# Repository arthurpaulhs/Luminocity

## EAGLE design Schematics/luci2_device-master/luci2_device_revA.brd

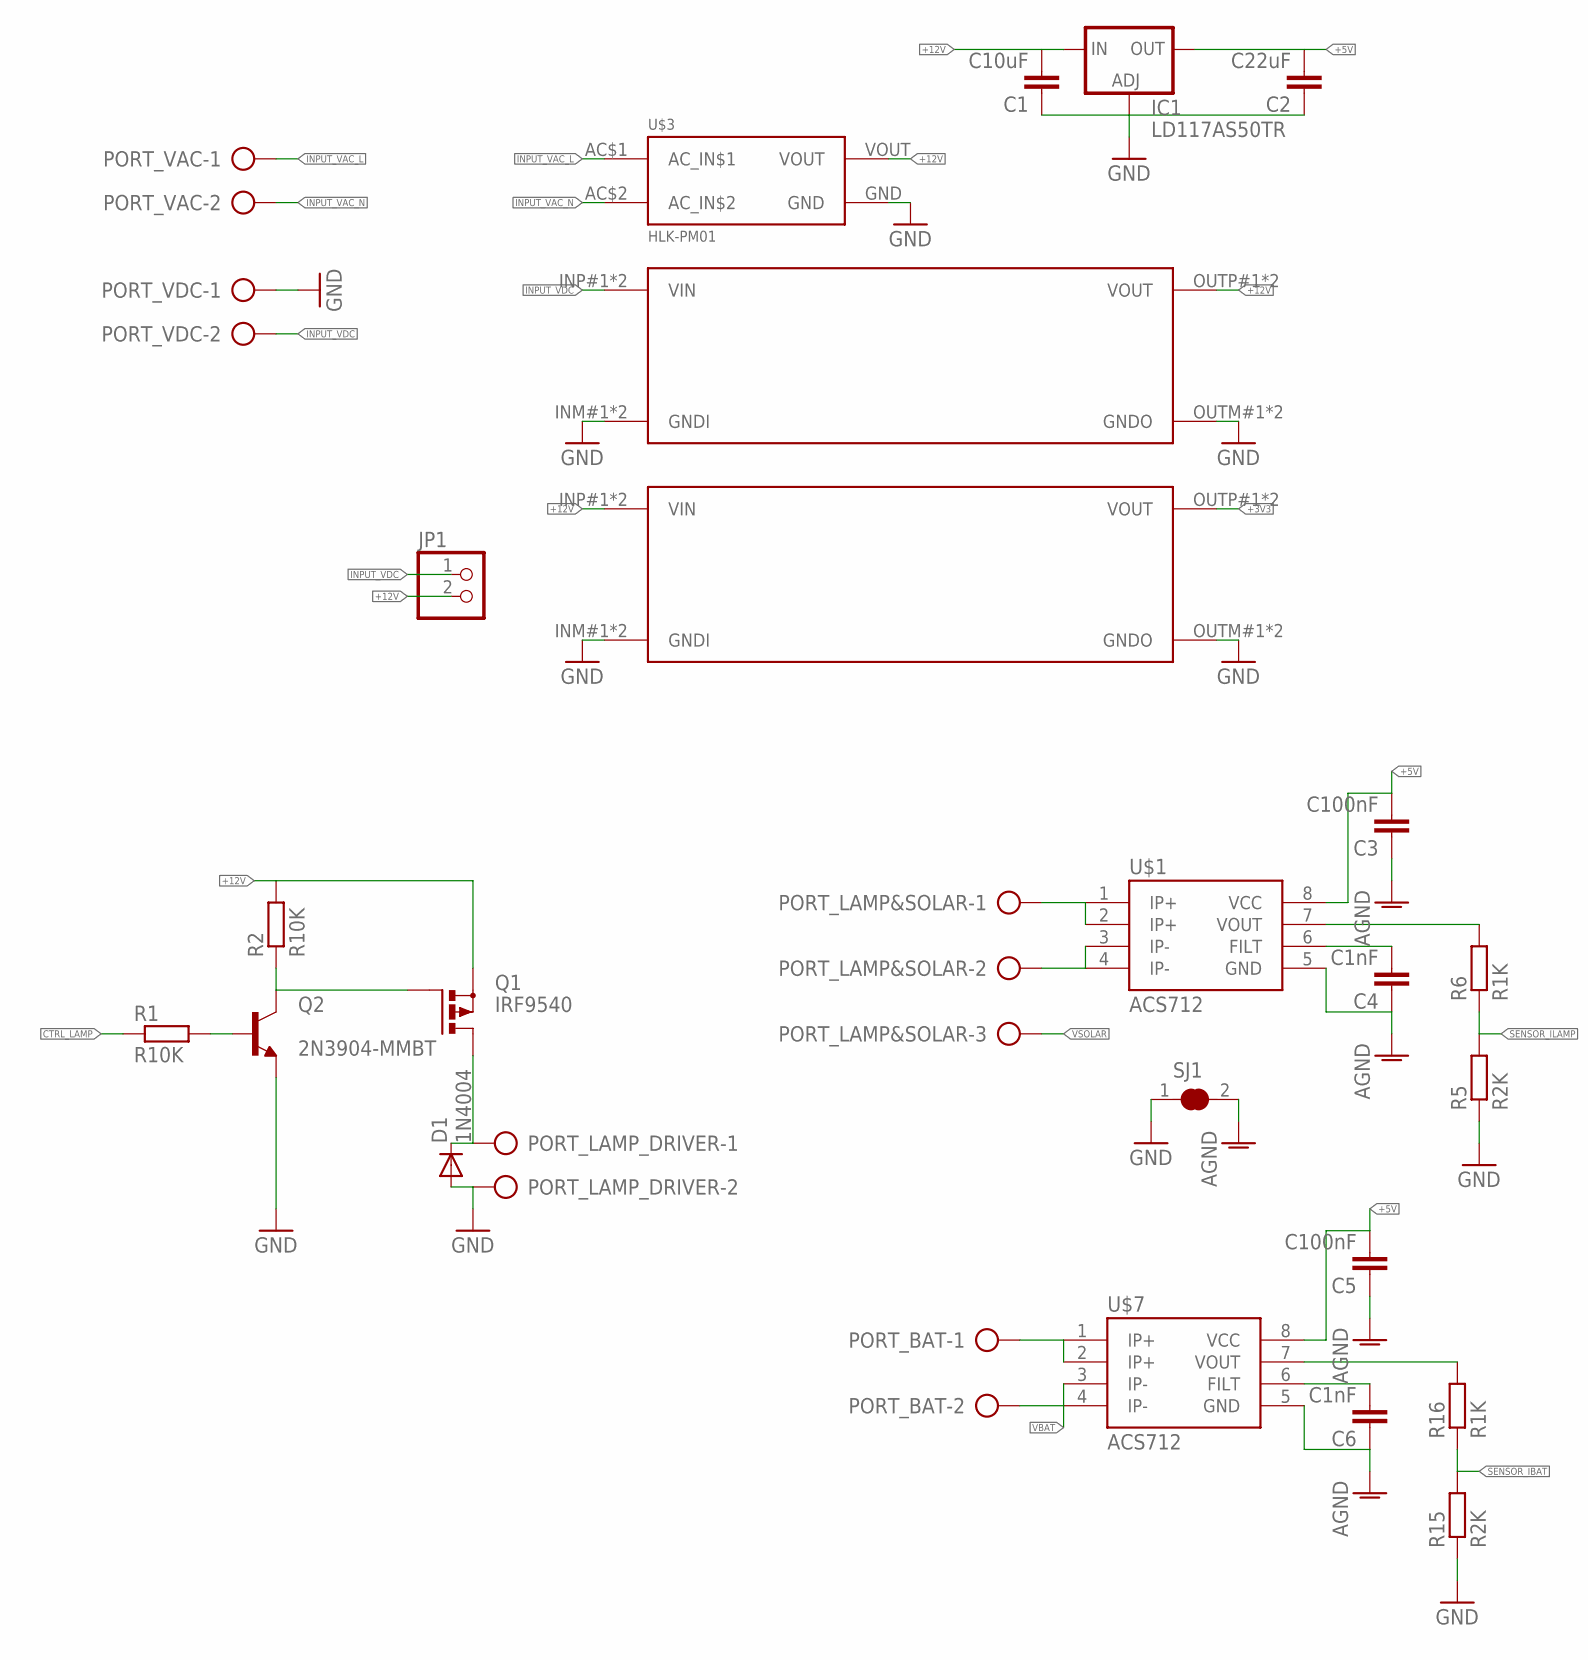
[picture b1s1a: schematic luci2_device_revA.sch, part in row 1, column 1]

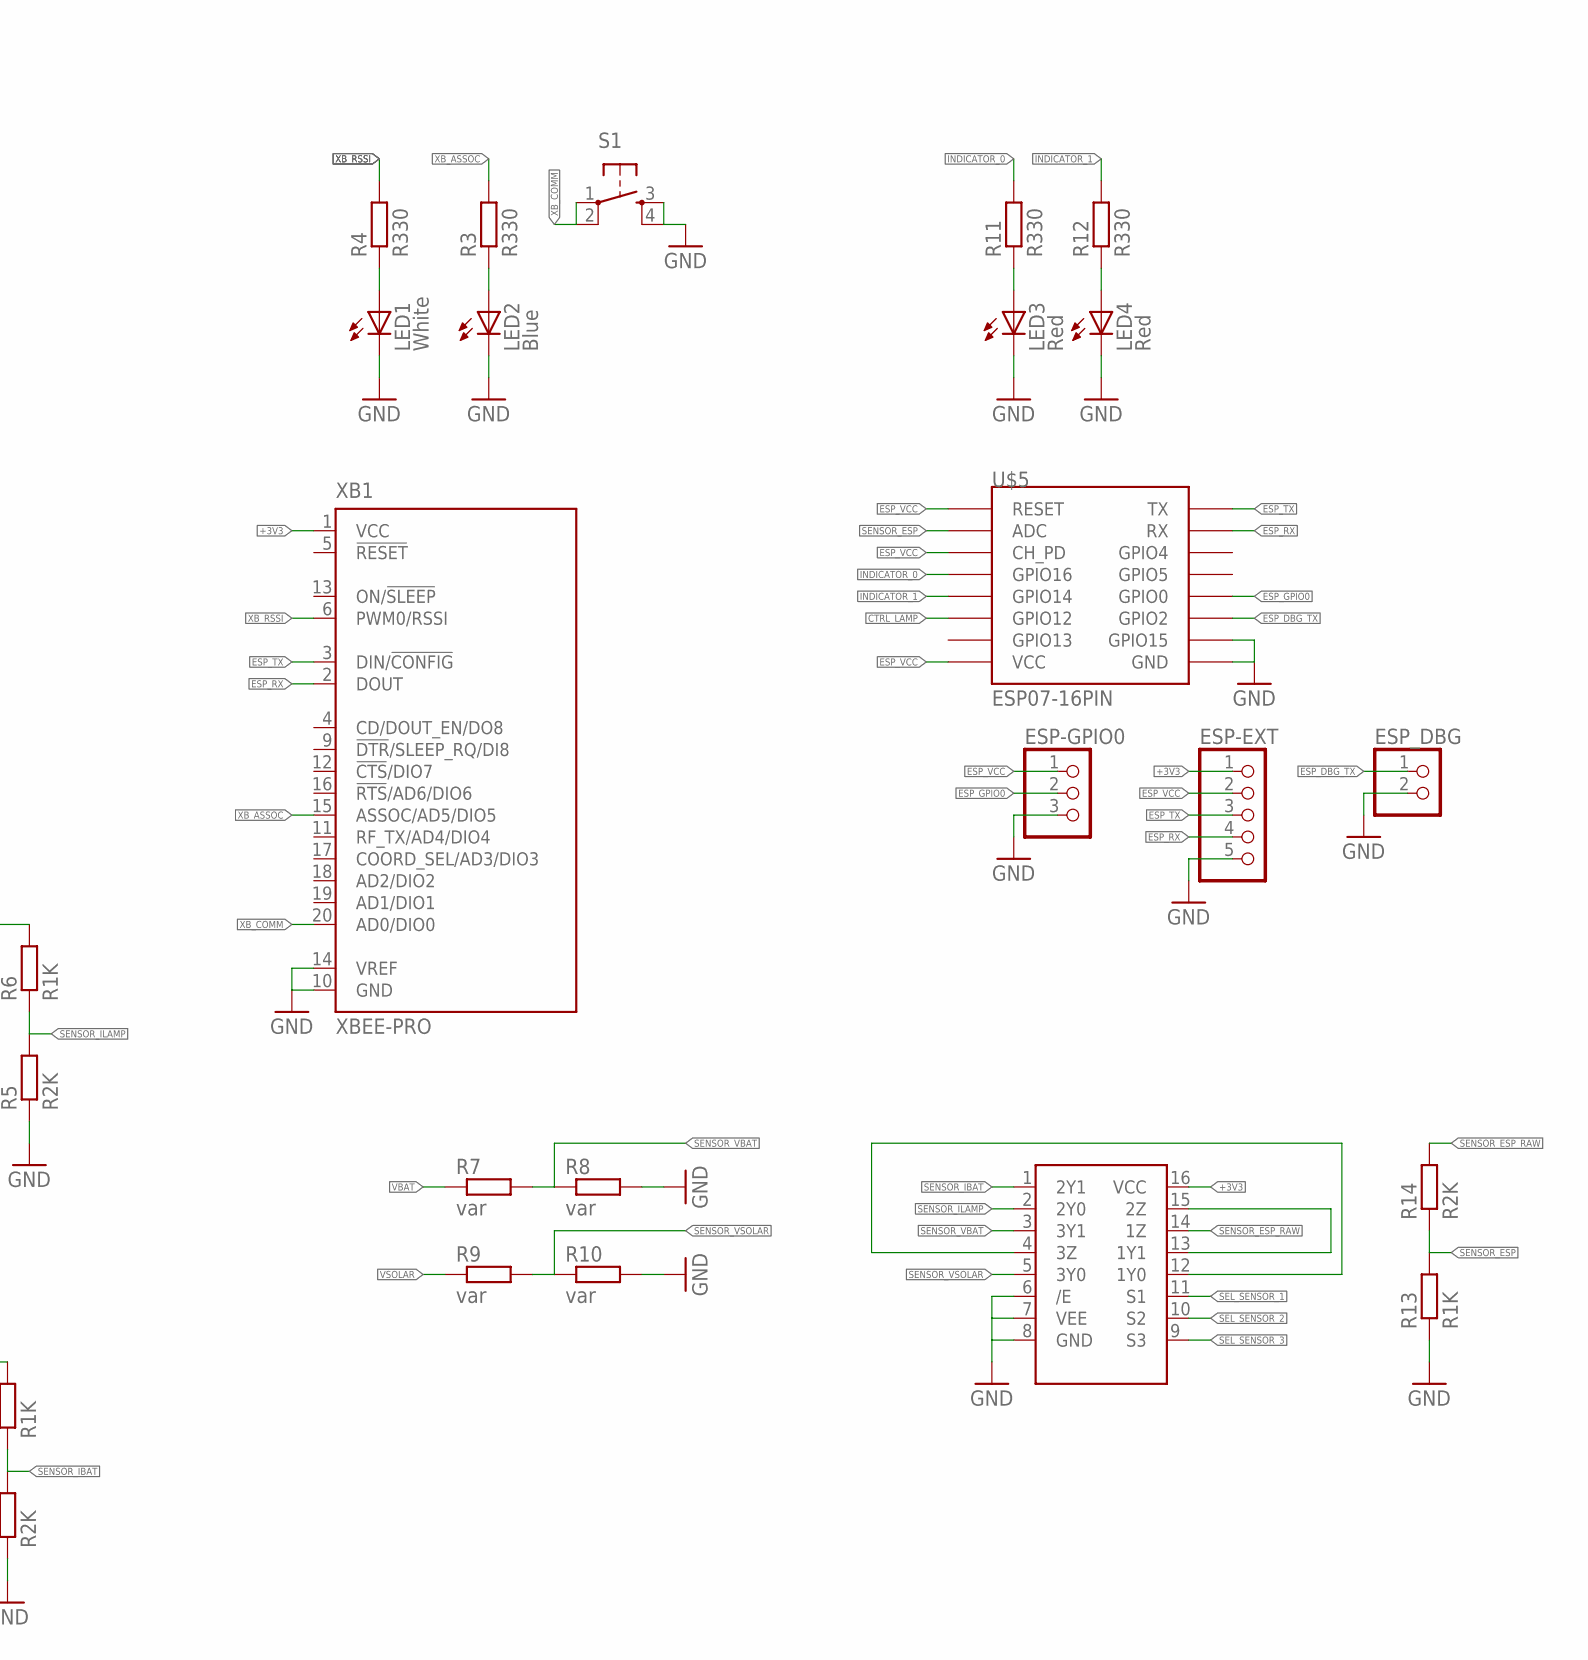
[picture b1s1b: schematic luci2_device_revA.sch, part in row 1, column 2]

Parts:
C1: C10uF; C0805
C2: C22uF; C0805
C3, C5: C100nF; C0805
C4, C6: C1nF; C0805
D1: 1N4004; DO41-10
ESP-EXT: HEADER-1X5ROUND; 1X05_ROUND
ESP-GPIO0: HEADER-1X3ROUND; 1X03_ROUND
ESP_DBG: HEADER-1X2ROUND; 1X02_ROUND
IC1: LD117AS50TR; SOT223
JP1: HEADER-1X2ROUND; 1X02_ROUND
LED1: White; CHIPLED_0805
LED2: Blue; CHIPLED_0805
LED3, LED4: Red; CHIPLED_0805
PORT_BAT: AK300/2
PORT_LAMP&SOLAR: AK300/3
PORT_LAMP_DRIVER: AK300/2
PORT_VAC: AK300/2
PORT_VDC: AK300/2
Q1: IRF9540; TO220BV
Q2: 2N3904-MMBT; SOT23
R1, R2: R10K; M0805
R3, R4, R11, R12: R330; M0805
R5, R14, R15: R2K; M0805
R6, R13, R16: R1K; M0805
R7, R8, R9, R10: var; M0805
S1: TAC_SWITCHPTH; TACTILE-PTH
SJ1: SOLDERJUMPER_CLOSED; SOLDERJUMPER_CLOSEDWIRE
U$1, U$7: ACS712; SO08
U$2, U$4: DCDCMODULE_SMALL; DCDCMODULE-SMALL
U$3: HLK-PM01
U$5: ESP07-16PIN
U$6: 74HC4053D; SO16
XB1: XBEE-PRO

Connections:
+3V3: ESP-EXT.1, U$2.OUTP#1 (VOUT), U$2.OUTP#2 (VOUT), U$6.16 (VCC), XB1.1 (VCC)
+5V: C2.2, C3.2, C5.2, IC1.4 (OUT), U$1.8 (VCC), U$7.8 (VCC)
+12V: C1.2, IC1.3 (IN), JP1.2, Q1.S, R2.2, U$2.INP#1 (VIN), U$2.INP#2 (VIN), U$3.VOUT, U$4.OUTP#1 (VOUT), U$4.OUTP#2 (VOUT)
AGND: C3.1, C4.1, C5.1, C6.1, SJ1.2, U$1.5 (GND), U$7.5 (GND)
CTRL_LAMP: R1.1, U$5.GPIO12
ESP_DBG_TX: ESP_DBG.1, U$5.GPIO2
ESP_GPIO0: ESP-GPIO0.2, U$5.GPIO0
ESP_RX: ESP-EXT.4, U$5.RX, XB1.2 (DOUT)
ESP_TX: ESP-EXT.3, U$5.TX, XB1.3 (DIN/!CONFIG)
ESP_VCC: ESP-EXT.2, ESP-GPIO0.1, U$5.CH_PD, U$5.REST (RESET), U$5.VCC
GND: C1.1, C2.1, D1.A, ESP-EXT.5, ESP-GPIO0.3, ESP_DBG.2, IC1.1 (ADJ), LED1.C, LED2.C, LED3.C, LED4.C, PORT_LAMP_DRIVER.2, PORT_VDC.1, Q2.2 (E), R5.1, R8.2, R10.2, R13.1, R15.1, S1.3, S1.4, SJ1.1, U$2.INM#1 (GNDI), U$2.INM#2 (GNDI), U$2.OUTM#1 (GNDO), U$2.OUTM#2 (GNDO), U$3.GND, U$4.INM#1 (GNDI), U$4.INM#2 (GNDI), U$4.OUTM#1 (GNDO), U$4.OUTM#2 (GNDO), U$5.GND, U$5.GPIO15, U$6.6 (/E), U$6.7 (VEE), U$6.8 (GND), XB1.10 (GND), XB1.14 (VREF)
INDICATOR_0: R11.2, U$5.GPIO16
INDICATOR_1: R12.2, U$5.GPIO14
INPUT_VAC_L: PORT_VAC.1, U$3.AC$1 (AC_IN$1)
INPUT_VAC_N: PORT_VAC.2, U$3.AC$2 (AC_IN$2)
INPUT_VDC: JP1.1, PORT_VDC.2, U$4.INP#1 (VIN), U$4.INP#2 (VIN)
unnamed: D1.C, PORT_LAMP_DRIVER.1, Q1.D
unnamed: Q1.G, Q2.3 (C), R2.1
unnamed: LED1.A, R4.1
unnamed: Q2.1 (B), R1.2
unnamed: LED2.A, R3.1
unnamed: U$6.13 (1Y1), U$6.15 (2Z)
unnamed: R6.2, U$1.7 (VOUT)
unnamed: PORT_LAMP&SOLAR.1, U$1.1 (IP+), U$1.2 (IP+)
unnamed: U$6.4 (3Z), U$6.12 (1Y0)
unnamed: PORT_LAMP&SOLAR.2, U$1.3 (IP-), U$1.4 (IP-)
unnamed: C4.2, U$1.6 (FILT)
unnamed: PORT_BAT.1, U$7.1 (IP+), U$7.2 (IP+)
unnamed: C6.2, U$7.6 (FILT)
unnamed: R16.2, U$7.7 (VOUT)
unnamed: LED3.A, R11.1
unnamed: LED4.A, R12.1
SEL_SENSOR_1: U$6.11 (S1)
SEL_SENSOR_2: U$6.10 (S2)
SEL_SENSOR_3: U$6.9 (S3)
SENSOR_ESP: R13.2, R14.1, U$5.ADC
SENSOR_ESP_RAW: R14.2, U$6.14 (1Z)
SENSOR_IBAT: R15.2, R16.1, U$6.1 (2Y1)
SENSOR_ILAMP: R5.2, R6.1, U$6.2 (2Y0)
SENSOR_VBAT: R7.2, R8.1, U$6.3 (3Y1)
SENSOR_VSOLAR: R9.2, R10.1, U$6.5 (3Y0)
VBAT: PORT_BAT.2, R7.1, U$7.3 (IP-), U$7.4 (IP-)
VSOLAR: PORT_LAMP&SOLAR.3, R9.1
XB_ASSOC: R3.2, XB1.15 (ASSOC/AD5/DIO5)
XB_COMM: S1.1, S1.2, XB1.20 (AD0/DIO0)
XB_RSSI: R4.2, XB1.6 (PWM0/RSSI)

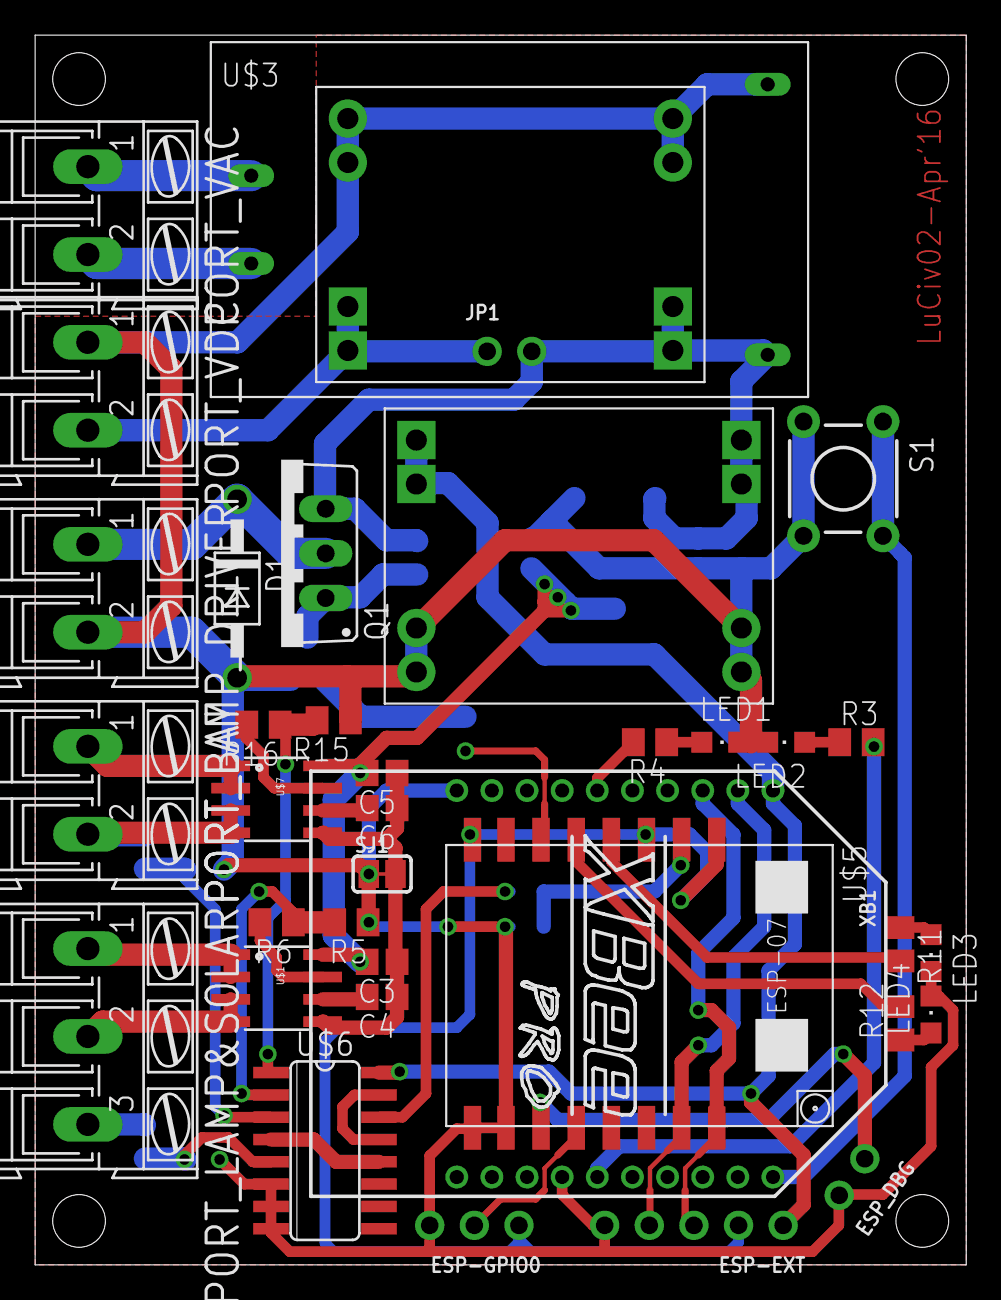
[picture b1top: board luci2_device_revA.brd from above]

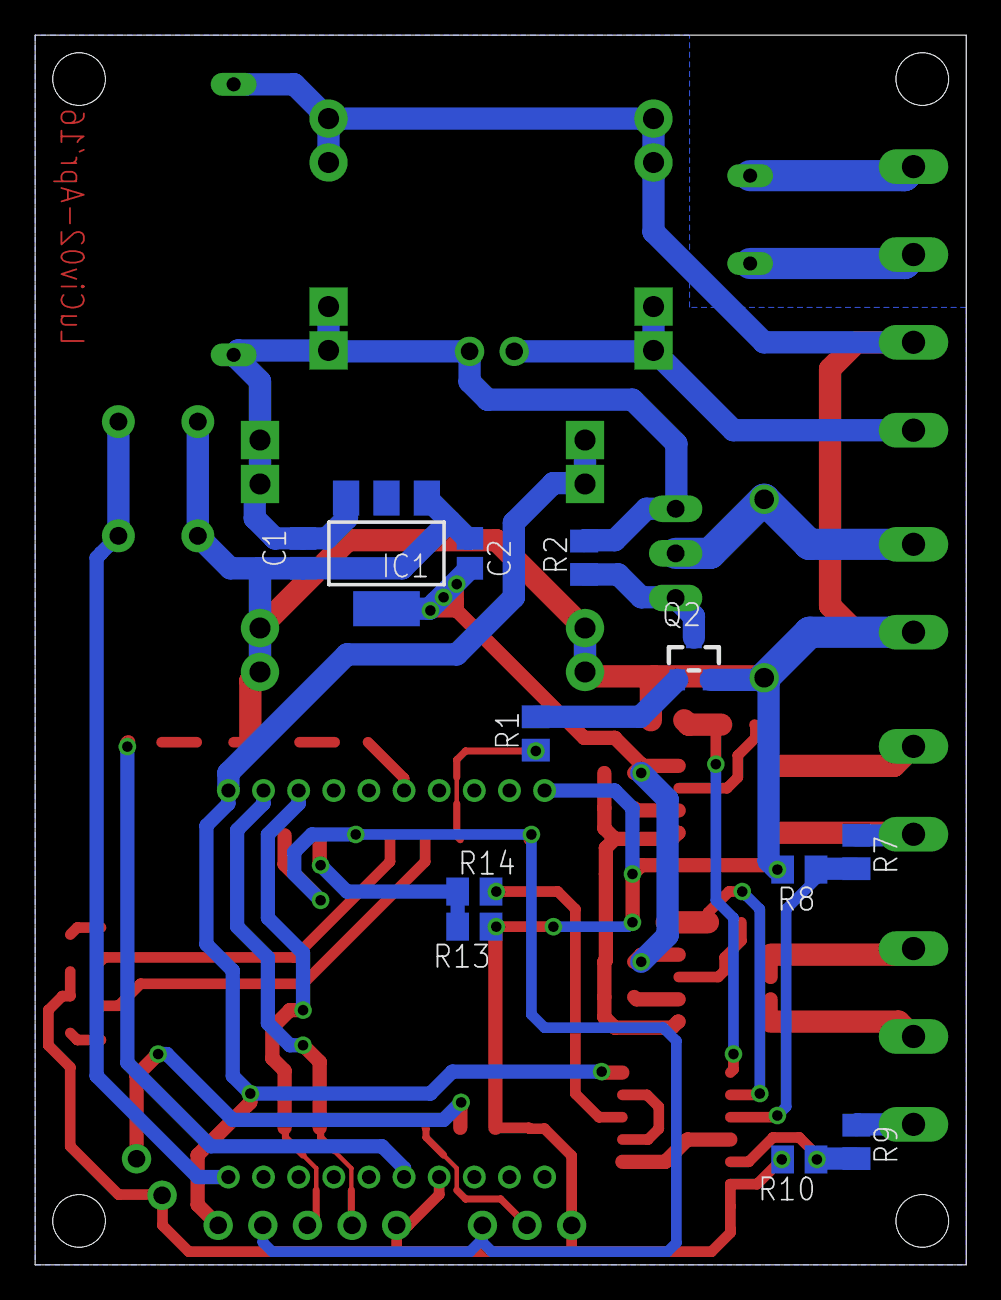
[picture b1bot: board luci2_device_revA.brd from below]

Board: 2 copper layers, 53.0 x 70.0 mm, 49 parts (12 on the bottom side), 43 nets.

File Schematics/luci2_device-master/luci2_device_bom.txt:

Partlist exported from C:/Users/tritronik/Documents/GitHub/luminocity2/luci2_boards/luci2_device/luci2_device.sch at 10/03/2016 10:14:19

Qty Value             Device            Package           Parts                                Description                            
3                     AK300/2           AK300/2           LOAD_LAMP_DRIVER, PORT_VAC, PORT_VDC CONNECTOR                              
1                     AK300/4           AK300/4           SENSOR1                              CONNECTOR                              
1                     HEADER-1X2ROUND   1X02_ROUND        JP1                                  PIN HEADER                             
2                     HEADER-1X3ROUND   1X03_ROUND        ARDU_DBG, ESP-GPIO0                  PIN HEADER                             
1                     HEADER-1X5ROUND   1X05_ROUND        ESP-EXT                              PIN HEADER                             
1                     TAC_SWITCHPTH     TACTILE-PTH       S1                                   Momentary Switch                       
1   1N4004            1N4004            DO41-10           D1                                   DIODE                                  
1   2N3904-MMBT       2N3904-MMBT       SOT23             Q2                                   NPN TRANSISTOR                         
1   ARDUINO_PRO_MICRO ARDUINO_PRO_MICRO ARDUINO_PRO_MICRO U$1                                                                         
1   Blue              LEDCHIPLED_0805   CHIPLED_0805      LED2                                 LED                                    
2   DCDCMODULE_SMALL  DCDCMODULE_SMALL  DCDCMODULE-SMALL  U$2, U$4                                                                    
1   ESP07-16PIN       ESP07-16PIN       ESP07-16PIN       U$5                                  ESP8266 Wifi module 07 - 16 pins       
1   HLK-PM01          HLK-PM01          HLK-PM01          U$3                                                                         
1   IRF9540           PMOSFET_PTO220BV  TO220BV           Q1                                   Power MOSFET P-Channel                 
2   R10K              R-EU_M0805        M0805             R1, R2                               RESISTOR, European symbol              
2   R1K               R-EU_M0805        M0805             R5, R15                              RESISTOR, European symbol              
2   R2K               R-EU_M0805        M0805             R6, R16                              RESISTOR, European symbol              
2   R330              R-EU_M0805        M0805             R3, R4                               RESISTOR, European symbol              
1   Red               LEDCHIPLED_0805   CHIPLED_0805      LED1                                 LED                                    
1   XBEE-PRO          XBEE-PRO          XBEE-PRO          XB1                                  XBee (TM) /XBee-PRO(TM) OEM RF Modules 
8   var               R-EU_M0805        M0805             R7, R8, R9, R10, R11, R12, R13, R14  RESISTOR, European symbol

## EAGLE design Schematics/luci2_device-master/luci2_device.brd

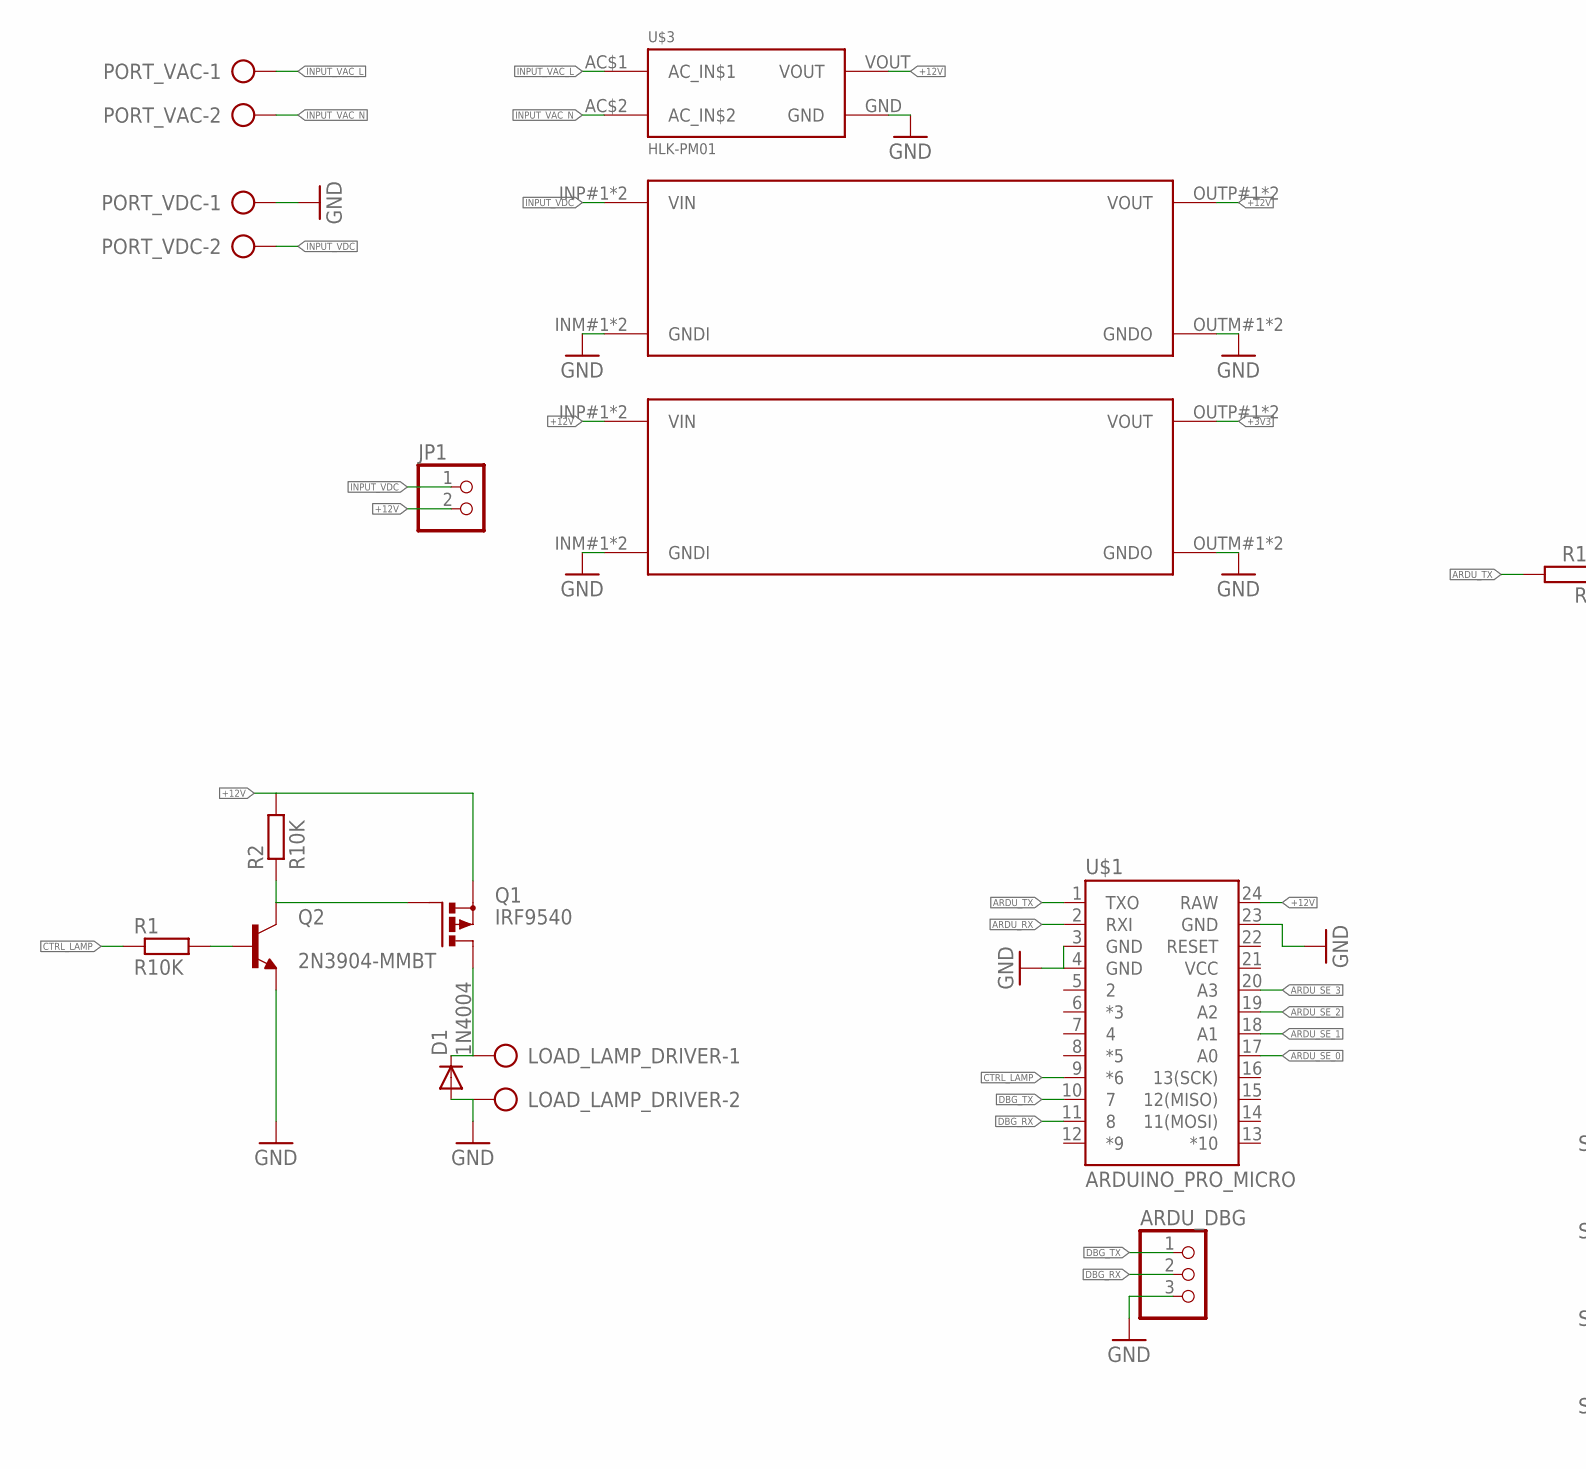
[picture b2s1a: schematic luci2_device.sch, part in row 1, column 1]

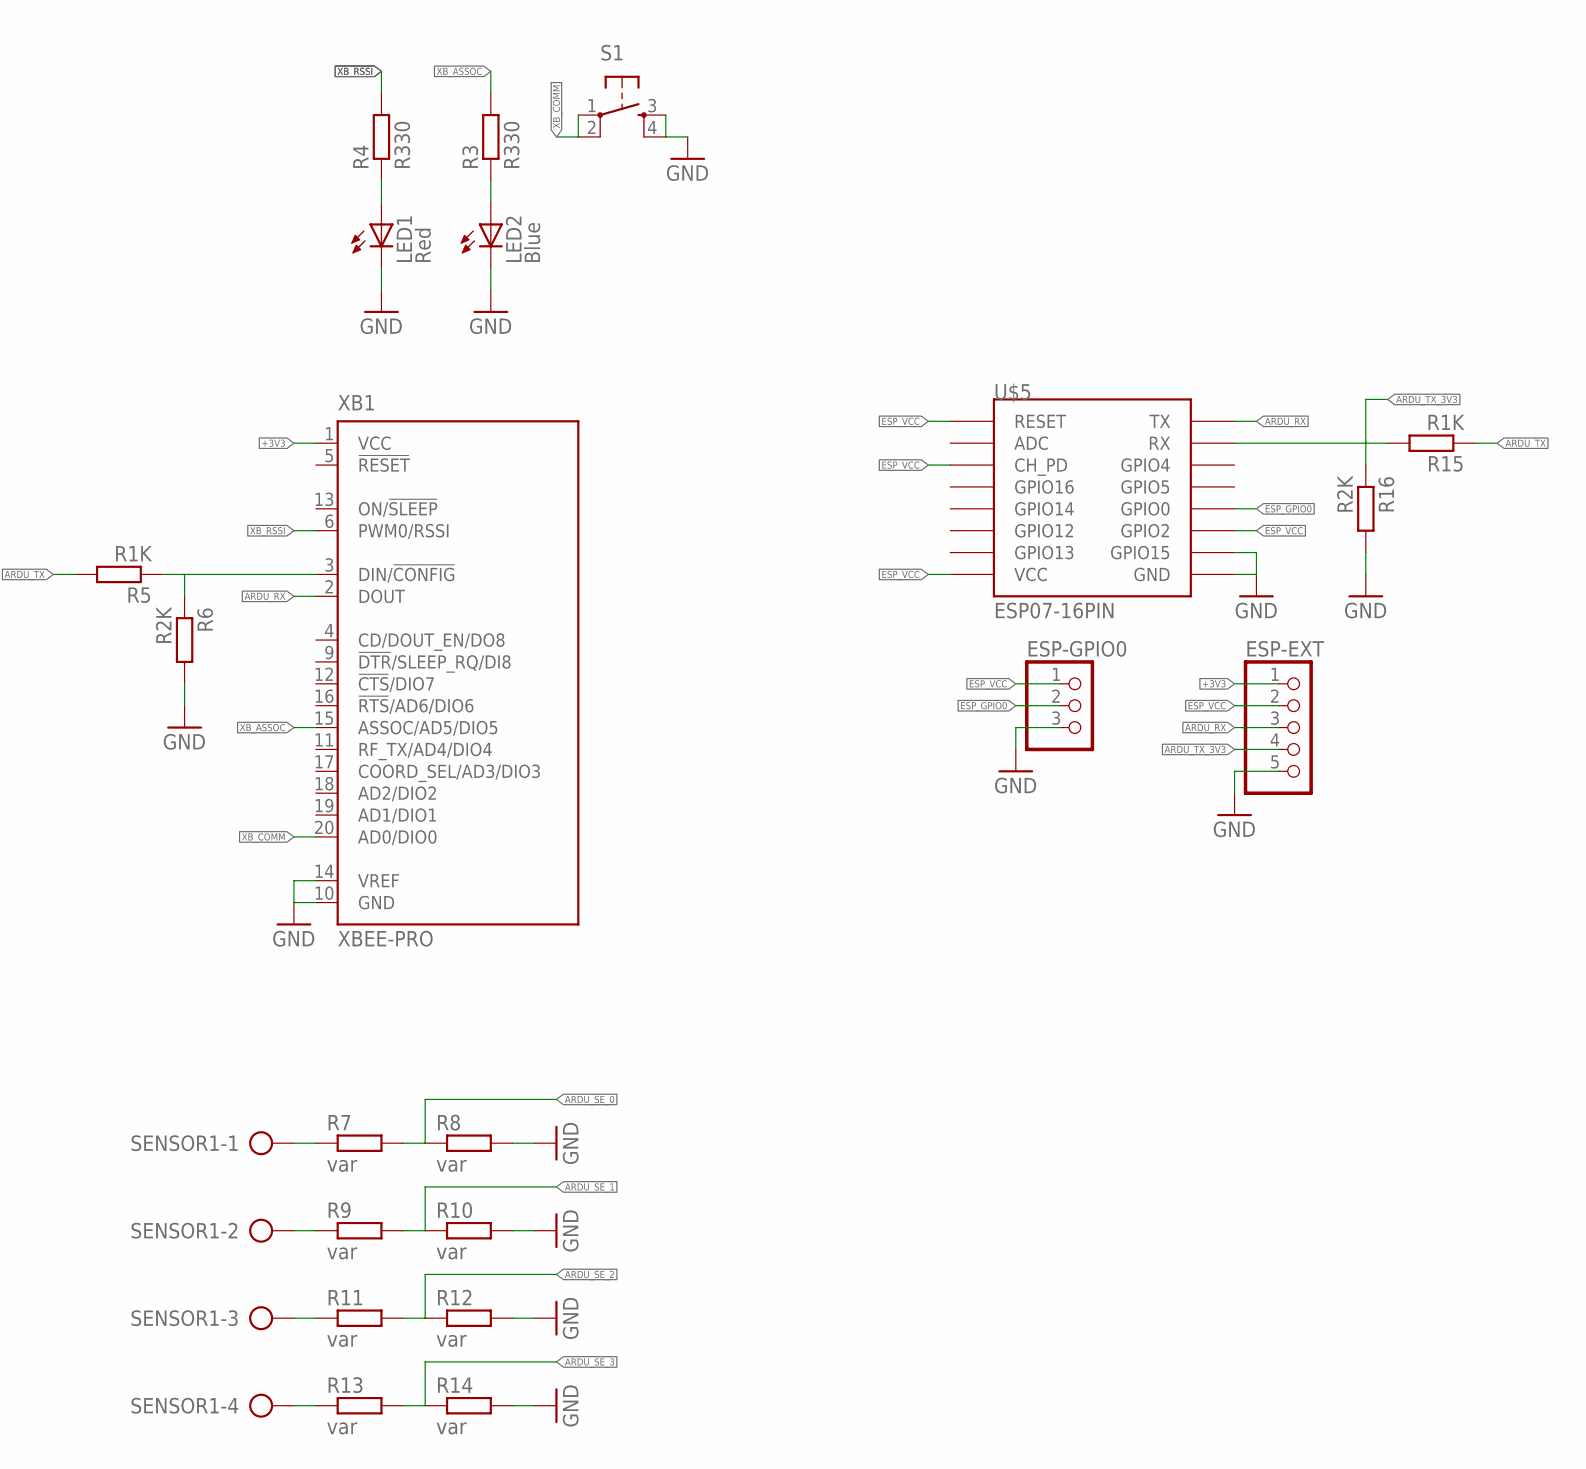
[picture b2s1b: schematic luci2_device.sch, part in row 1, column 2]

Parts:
ARDU_DBG: HEADER-1X3ROUND; 1X03_ROUND
D1: 1N4004; DO41-10
ESP-EXT: HEADER-1X5ROUND; 1X05_ROUND
ESP-GPIO0: HEADER-1X3ROUND; 1X03_ROUND
JP1: HEADER-1X2ROUND; 1X02_ROUND
LED1: Red; CHIPLED_0805
LED2: Blue; CHIPLED_0805
LOAD_LAMP_DRIVER: AK300/2
PORT_VAC: AK300/2
PORT_VDC: AK300/2
Q1: IRF9540; TO220BV
Q2: 2N3904-MMBT; SOT23
R1, R2: R10K; M0805
R3, R4: R330; M0805
R5, R15: R1K; M0805
R6, R16: R2K; M0805
R7, R8, R9, R10, R11, R12, R13, R14: var; M0805
S1: TAC_SWITCHPTH; TACTILE-PTH
SENSOR1: AK300/4
U$1: ARDUINO_PRO_MICRO
U$2, U$4: DCDCMODULE_SMALL; DCDCMODULE-SMALL
U$3: HLK-PM01
U$5: ESP07-16PIN
XB1: XBEE-PRO

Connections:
+3V3: ESP-EXT.1, U$2.OUTP#1 (VOUT), U$2.OUTP#2 (VOUT), XB1.1 (VCC)
+12V: JP1.2, Q1.S, R2.2, U$1.24 (RAW), U$2.INP#1 (VIN), U$2.INP#2 (VIN), U$3.VOUT, U$4.OUTP#1 (VOUT), U$4.OUTP#2 (VOUT)
ARDU_RX: ESP-EXT.3, U$1.2 (RXI), U$5.TX, XB1.2 (DOUT)
ARDU_SE_0: R7.2, R8.1, U$1.17 (A0)
ARDU_SE_1: R9.2, R10.1, U$1.18 (A1)
ARDU_SE_2: R11.2, R12.1, U$1.19 (A2)
ARDU_SE_3: R13.2, R14.1, U$1.20 (A3)
ARDU_TX: R5.2, R15.1, U$1.1 (TXO)
ARDU_TX_3V3: ESP-EXT.4, R15.2, R16.1, U$5.RX
CTRL_LAMP: R1.1, U$1.9 (*6)
DBG_RX: ARDU_DBG.2, U$1.11 (8)
DBG_TX: ARDU_DBG.1, U$1.10 (7)
ESP_GPIO0: ESP-GPIO0.2, U$5.GPIO0
ESP_VCC: ESP-EXT.2, ESP-GPIO0.1, U$5.CH_PD, U$5.GPIO2, U$5.REST (RESET), U$5.VCC
GND: ARDU_DBG.3, D1.A, ESP-EXT.5, ESP-GPIO0.3, LED1.C, LED2.C, LOAD_LAMP_DRIVER.2, PORT_VDC.1, Q2.2 (E), R6.2, R8.2, R10.2, R12.2, R14.2, R16.2, S1.3, S1.4, U$1.3 (GND), U$1.4 (GND), U$1.23 (GND), U$2.INM#1 (GNDI), U$2.INM#2 (GNDI), U$2.OUTM#1 (GNDO), U$2.OUTM#2 (GNDO), U$3.GND, U$4.INM#1 (GNDI), U$4.INM#2 (GNDI), U$4.OUTM#1 (GNDO), U$4.OUTM#2 (GNDO), U$5.GND, U$5.GPIO15, XB1.10 (GND), XB1.14 (VREF)
INPUT_VAC_L: PORT_VAC.1, U$3.AC$1 (AC_IN$1)
INPUT_VAC_N: PORT_VAC.2, U$3.AC$2 (AC_IN$2)
INPUT_VDC: JP1.1, PORT_VDC.2, U$4.INP#1 (VIN), U$4.INP#2 (VIN)
unnamed: D1.C, LOAD_LAMP_DRIVER.1, Q1.D
unnamed: Q1.G, Q2.3 (C), R2.1
unnamed: LED1.A, R4.1
unnamed: Q2.1 (B), R1.2
unnamed: LED2.A, R3.1
unnamed: R5.1, R6.1, XB1.3 (DIN/!CONFIG)
unnamed: R7.1, SENSOR1.1
unnamed: R9.1, SENSOR1.2
unnamed: R11.1, SENSOR1.3
unnamed: R13.1, SENSOR1.4
XB_ASSOC: R3.2, XB1.15 (ASSOC/AD5/DIO5)
XB_COMM: S1.1, S1.2, XB1.20 (AD0/DIO0)
XB_RSSI: R4.2, XB1.6 (PWM0/RSSI)

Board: 2 copper layers, 36 parts (1 on the bottom side), 31 nets, no tracks yet.

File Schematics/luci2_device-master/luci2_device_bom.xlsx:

No | Component | Unit | Unit Price | Component Price | Reference
1 | AK300/2 | 3 | 0.1 | 0.30000000000000004 | link
2 | AK300/4 | 1 | 0.2 | 0.2 | link
3 | HEADER-1X2ROUND | 1 | 0.3 | 0.3 | link
4 | HEADER-1X3ROUND
5 | HEADER-1X5ROUND
6 | TAC_SWITCHPTH | 1 | 0.1 | 0.1 | link
7 | 1N4004 | 1 | 0.1 | 0.1 | link
8 | 2N3904-MMBT | 1 | 0.1 | 0.1 | link
9 | ARDUINO_PRO_MICRO | 1 | 3.4 | 3.4 | link
10 | LEDCHIPLED_0805 | 1 | 0.1 | 0.1 | JP
11 | DCDCMODULE_SMALL | 2 | 1.2 | 2.4 | link
12 | ESP07-16PIN | 1 | 2.5 | 2.5 | link
13 | HLK-PM01 | 1 | 4 | 4 | link
14 | PMOSFET_PTO220BV | 1 | 1 | 1 | link
15 | R-EU_M0805 | 1 | 1 | 1 | JP
16 | R-EU_M0805
17 | R-EU_M0805
18 | R-EU_M0805
19 | R-EU_M0805
20 | LEDCHIPLED_0805 | 1 | 0.1 | 0.1 | JP
21 | XBEE-PRO | 1 | 17.5 | 17.5 | link
22 | XBEE-HEADER | 2 | 0.5 | 1 | link
23 | XBEE-ANTENNA | 1 | 2.5 | 2.5 | link
24 | WIFI-ANTENNA | 1 | 1.1000000000000001 | 1.1000000000000001 | link
25 | ARDUINO-HEADER | 1 | 0.5 | 0.5 | JP
Jumlah |  |  |  | 38.200000000000003
Smallest unit price is USD 0,1
Currency in USD

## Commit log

2016-07-13 :boom::camel: Added .gitattributes & .gitignore files
2016-07-13 Initial changes
    Added codes and schematics
2016-07-15 WiFi Manager library removed
    Use of WiFi Manager library for credentials entry removed due to
    performance inconsistencies.
2016-07-17 Add 5 seconds delay to handleSetAccessPoint() procedure
2016-07-17 Remove lucy_wifi broker.ino code
2016-07-17 Create new program to check mqtt connection
2016-07-17 Remove dependencies to WiFi manager library
2016-07-17 Revert "Remove dependencies to WiFi manager library"
    This reverts commit 7ddc9f505449b6533368c53306ebfd8580ca61f2.
2016-07-17 Remove dependency to WiFi manager library
    This reverts commit 2e497bd3ec77ac6f69e7d56f12a59148aab5f5cf.
2016-07-18 Improve visual appearance of debugging window
2016-07-18 Improve web server layout
2016-07-22 Fix voltage measurement error and esp8266 float publish problem
2016-08-08 Fix current measurement error
2016-08-09 Control feature tested
2016-08-09 Create luminocity firmware

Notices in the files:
parts and their libraries:
SparkFun-Boards: Licensing: Creative Commons ShareAlike 4.0 International - https://creativecommons.org/licenses/by-sa/4.0
m-pad-2.1: License : GNU General Public License version 2 (see bottom)
